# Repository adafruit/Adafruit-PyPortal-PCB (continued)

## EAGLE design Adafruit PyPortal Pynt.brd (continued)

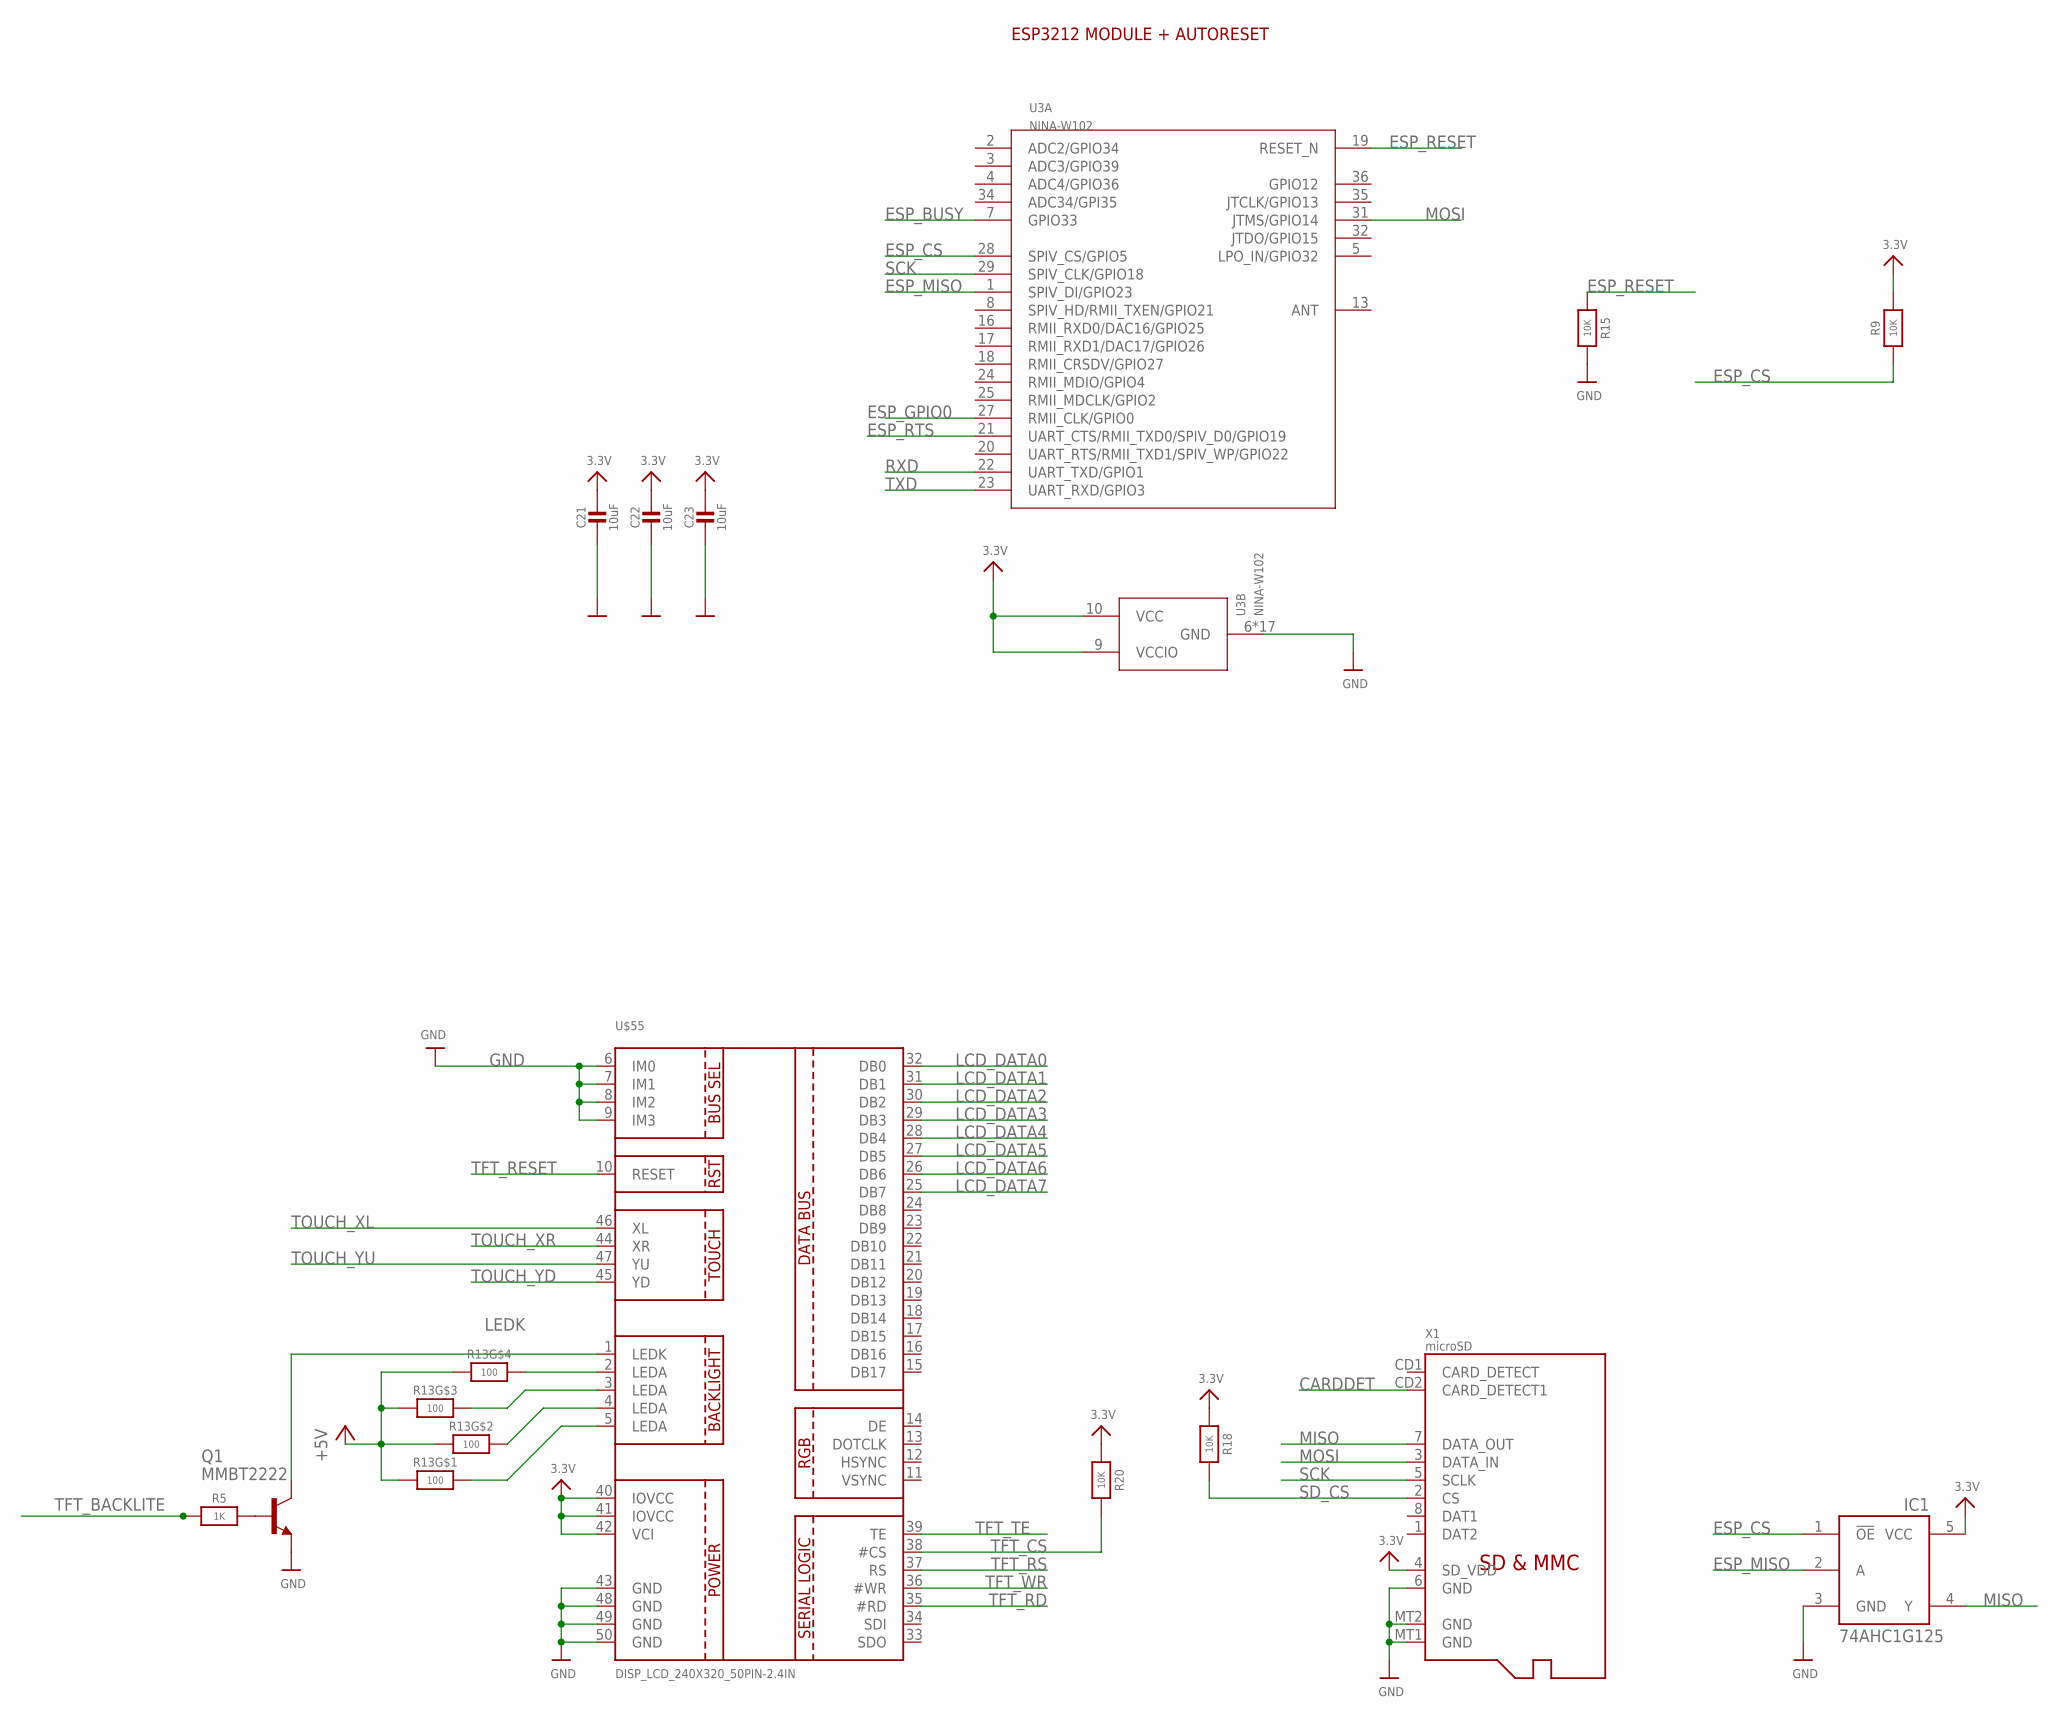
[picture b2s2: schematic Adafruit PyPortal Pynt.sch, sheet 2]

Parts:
C21, C22, C23: 10uF; 0805-NO
IC1: 74AHC1G125; SOT23-5L
Q1: MMBT2222; SOT23-BEC
R5: 1K; 0603-NO
R9, R15, R18, R20: 10K; 0603-NO
R13: 100; RESPACK_4X0603
U3: NINA-W102; ARDUINO-UCS&SOCS_NINA-W1X
U$55: DISP_LCD_240X320_50PIN-2.4IN; TFT_2.4IN_240X320_50PIN
X1: microSD; MICROSD

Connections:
3.3V: C21.1, C22.1, C23.1, IC1.5 (VCC), R9.2, R18.1, R20.1, U3.9 (VCCIO), U3.10 (VCC), U$55.40 (IOVCC), U$55.41 (IOVCC), U$55.42 (VCI), X1.4 (SD_VDD); also elsewhere on the board
+5V: R13.1, R13.2 (1), R13.3 (1), R13.4 (1); also elsewhere on the board
CARDDET: X1.CD2 (CARD_DETECT1); also elsewhere on the board
ESP_BUSY: U3.7 (GPIO33); also elsewhere on the board
ESP_CS: IC1.1 (!OE), R9.1, U3.28 (SPIV_CS/GPIO5); also elsewhere on the board
ESP_GPIO0: U3.27 (RMII_CLK/GPIO0); also elsewhere on the board
ESP_MISO: IC1.2 (A), U3.1 (SPIV_DI/GPIO23)
ESP_RESET: R15.1, U3.19 (RESET_N); also elsewhere on the board
ESP_RTS: U3.21 (UART_CTS/RMII_TXD0/SPIV_D0/GPIO19); also elsewhere on the board
GND: C21.2, C22.2, C23.2, IC1.3 (GND), Q1.E, R15.2, U3.6 (GND), U3.12 (GND), U3.14 (GND), U3.26 (GND), U3.30 (GND), U3.GND@1 (GND), U3.GND@2 (GND), U3.GND@3 (GND), U3.GND@4 (GND), U3.GND@5 (GND), U3.GND@6 (GND), U3.GND@7 (GND), U3.GND@8 (GND), U3.GND@9 (GND), U3.GND@10 (GND), U3.GND@11 (GND), U3.GND@12 (GND), U$55.6 (IM0), U$55.7 (IM1), U$55.8 (IM2), U$55.9 (IM3), U$55.43 (GND), U$55.48 (GND), U$55.49 (GND), U$55.50 (GND), X1.6 (GND), X1.MT1 (GND), X1.MT2 (GND); also elsewhere on the board
LCD_DATA0: U$55.32 (DB0); also elsewhere on the board
LCD_DATA1: U$55.31 (DB1); also elsewhere on the board
LCD_DATA2: U$55.30 (DB2); also elsewhere on the board
LCD_DATA3: U$55.29 (DB3); also elsewhere on the board
LCD_DATA4: U$55.28 (DB4); also elsewhere on the board
LCD_DATA5: U$55.27 (DB5); also elsewhere on the board
LCD_DATA6: U$55.26 (DB6); also elsewhere on the board
LCD_DATA7: U$55.25 (DB7); also elsewhere on the board
LEDK: Q1.C, U$55.1 (LEDK)
MISO: IC1.4 (Y), X1.7 (DATA_OUT); also elsewhere on the board
MOSI: U3.31 (JTMS/GPIO14), X1.3 (DATA_IN); also elsewhere on the board
unnamed: R13.8 (2), U$55.5 (LEDA)
unnamed: R13.5 (2), U$55.2 (LEDA)
unnamed: R13.6 (2), U$55.3 (LEDA)
unnamed: R13.7 (2), U$55.4 (LEDA)
unnamed: Q1.B, R5.2
RXD: U3.22 (UART_TXD/GPIO1); also elsewhere on the board
SCK: U3.29 (SPIV_CLK/GPIO18), X1.5 (SCLK); also elsewhere on the board
SD_CS: R18.2, X1.2 (CS); also elsewhere on the board
TFT_BACKLITE: R5.1; also elsewhere on the board
TFT_CS: R20.2, U$55.38 (#CS); also elsewhere on the board
TFT_RD: U$55.35 (#RD); also elsewhere on the board
TFT_RESET: U$55.10 (RESET); also elsewhere on the board
TFT_RS: U$55.37 (RS); also elsewhere on the board
TFT_TE: U$55.39 (TE); also elsewhere on the board
TFT_WR: U$55.36 (#WR); also elsewhere on the board
TOUCH_XL: U$55.46 (XL); also elsewhere on the board
TOUCH_XR: U$55.44 (XR); also elsewhere on the board
TOUCH_YD: U$55.45 (YD); also elsewhere on the board
TOUCH_YU: U$55.47 (YU); also elsewhere on the board
TXD: U3.23 (UART_RXD/GPIO3); also elsewhere on the board

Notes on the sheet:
ESP3212 MODULE + AUTORESET

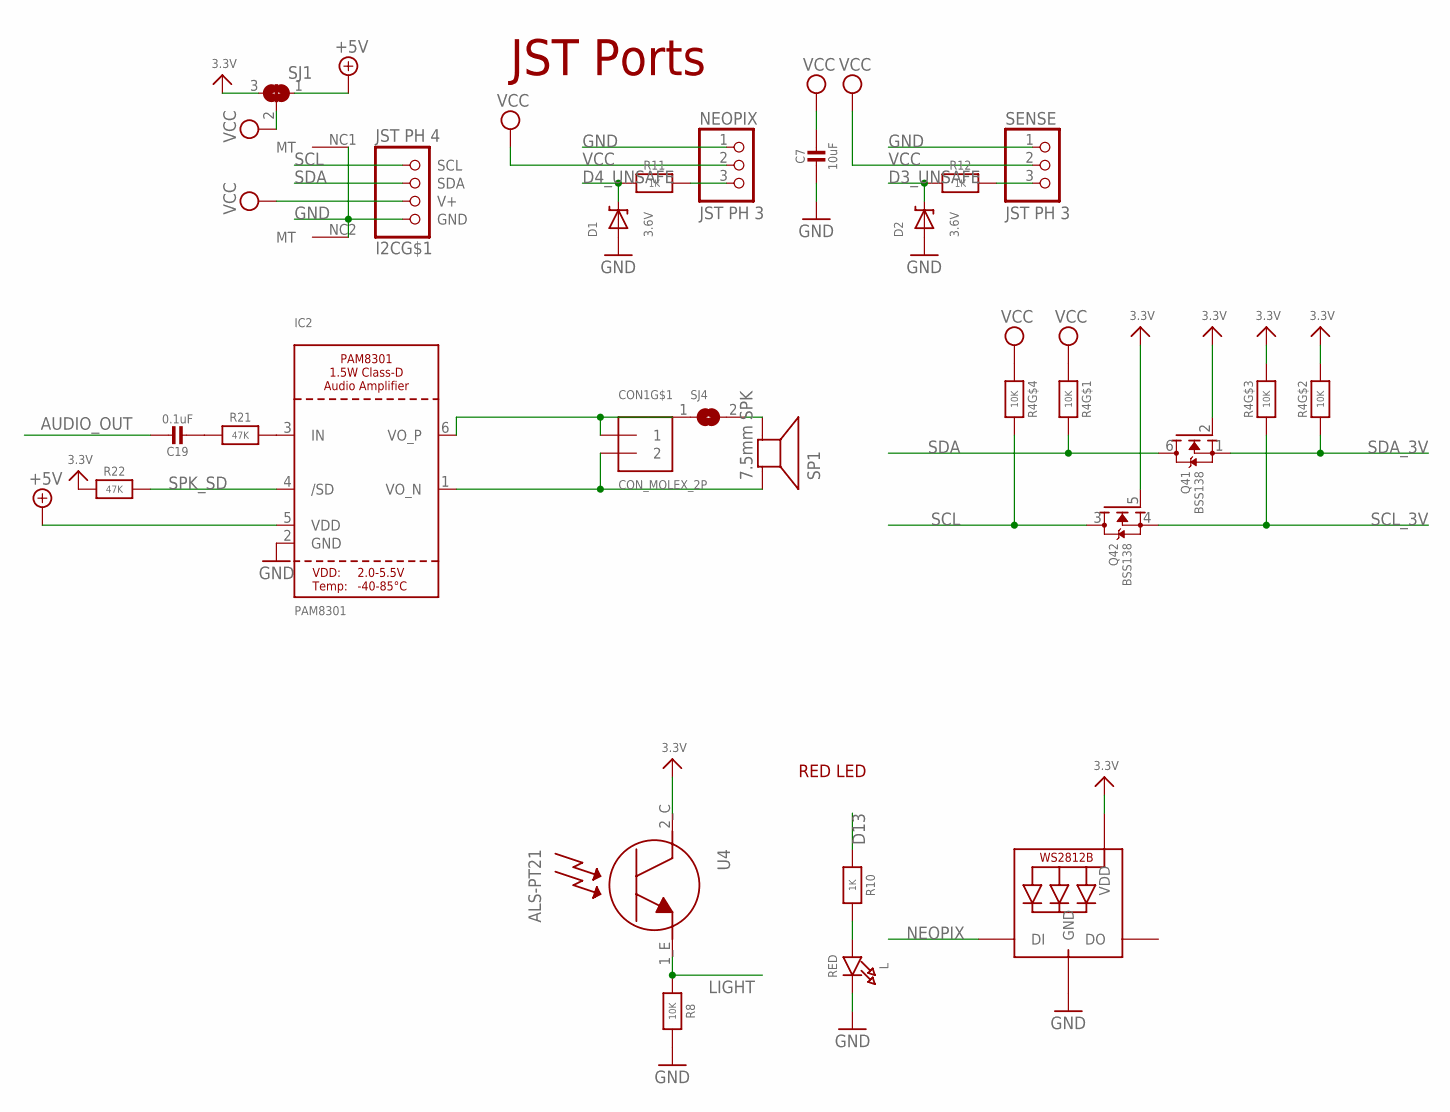
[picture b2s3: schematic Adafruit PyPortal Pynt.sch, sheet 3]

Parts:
C7: 10uF; 0805-NO
C19: 0.1uF; 0603-NO
CON1: CON_MOLEX_2P; 53398-0271
D1, D2: 3.6V; SOD-323
I2C: JST PH 4; JSTPH4
IC2: PAM8301; SOT23-6
L: RED; CHIPLED_0805_NOOUTLINE
LED1: WS2812B3535; LED3535
NEOPIX: JST PH 3; JSTPH3
Q4: BSS138; SOT363
R4: 10K; RESPACK_4X0603
R8: 10K; 0603-NO
R10, R11, R12: 1K; 0603-NO
R21, R22: 47K; 0603-NO
SENSE: JST PH 3; JSTPH3
SJ1: SOLDERJUMPER_2WAY; SOLDERJUMPER_2WAY_OPEN_NOPASTE
SJ4: SOLDERJUMPERCLOSED; SOLDERJUMPER_CLOSEDWIRE
SP1: 7.5mm SPK; BUZZER_SMT_7.5MM
U4: ALS-PT21; ALS-PT26-21C

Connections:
3.3V: LED1.2 (VDD), Q4.2 (G), Q4.5 (G), R4.2 (1), R4.3 (1), R22.1, SJ1.3, U4.2_C (C); also elsewhere on the board
+5V: IC2.5 (VDD), SJ1.1; also elsewhere on the board
AUDIO_OUT: C19.1; also elsewhere on the board
D3: R12.1, SENSE.3
D3_UNSAFE: D2.C, R12.2; also elsewhere on the board
D4: NEOPIX.3, R11.1
D4_UNSAFE: D1.C, R11.2; also elsewhere on the board
D13: R10.1; also elsewhere on the board
GND: C7.2, D1.A, D2.A, I2C.1 (GND), I2C.NC1 (MT), I2C.NC2 (MT), IC2.2 (GND), L.C, LED1.4 (GND), NEOPIX.1, R8.1, SENSE.1; also elsewhere on the board
LIGHT: R8.2, U4.1_E (E); also elsewhere on the board
unnamed: L.A, R10.2
unnamed: C19.2, R21.1
unnamed: IC2.3 (IN), R21.2
unnamed: SJ4.2, SP1.-
NEOPIX: LED1.1 (DI); also elsewhere on the board
SCL: I2C.4 (SCL), Q4.3 (D), R4.5 (2)
SCL_3V: Q4.4 (S), R4.6 (2); also elsewhere on the board
SDA: I2C.3 (SDA), Q4.6 (D), R4.8 (2)
SDA_3V: Q4.1 (S), R4.7 (2); also elsewhere on the board
SPKR+: CON1.2, IC2.1 (VO_N), SP1.+
SPK_SD: IC2.4 (/SD), R22.2; also elsewhere on the board
SPRK-: CON1.1, IC2.6 (VO_P), SJ4.1
VCC: C7.1, I2C.2 (V+), NEOPIX.2, R4.1, R4.4 (1), SENSE.2, SJ1.2

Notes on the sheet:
RED LED
JST Ports

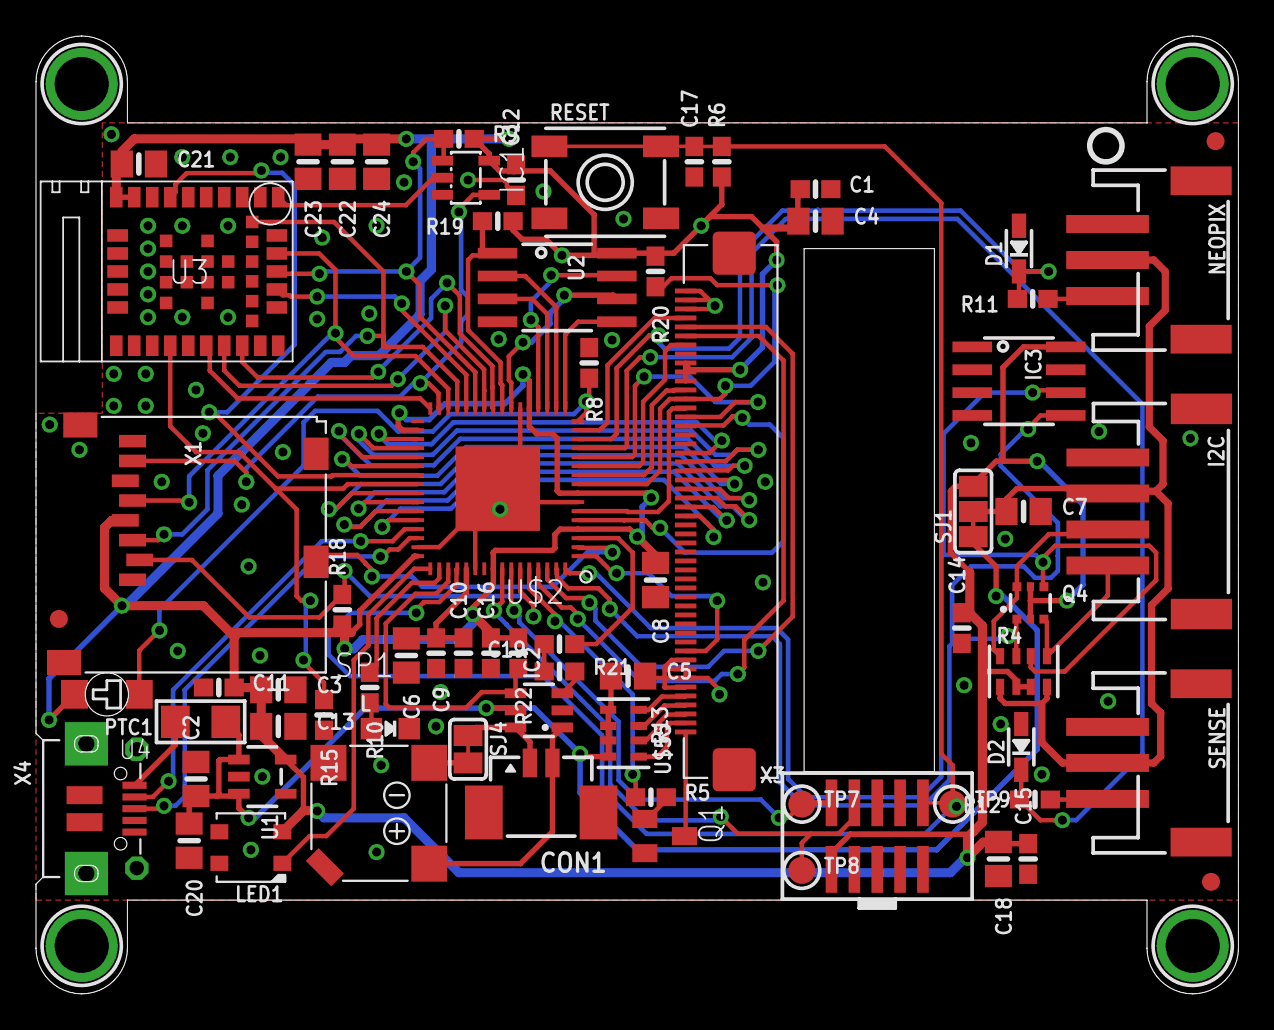
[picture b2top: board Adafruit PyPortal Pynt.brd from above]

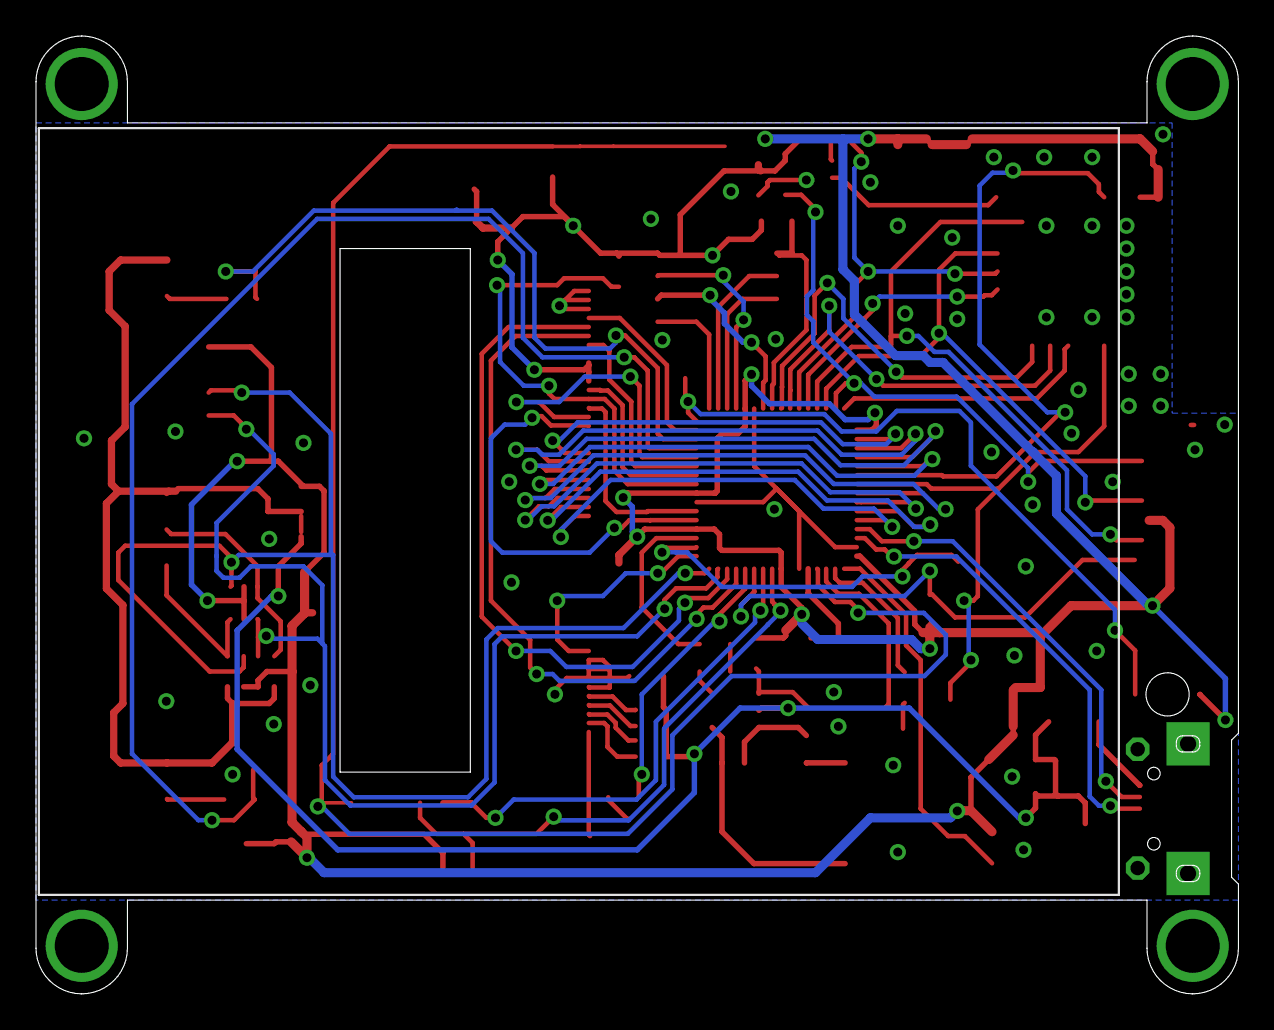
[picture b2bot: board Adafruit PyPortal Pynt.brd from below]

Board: 2 copper layers, 66.8 x 53.2 mm, 79 parts (2 on the bottom side), 74 nets.

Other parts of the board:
U$19: PYPORTALPYNT_TOP
U$54: PYPORTALPYNT_BOT
U$63: PCBFEAT-REV-040

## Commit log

2019-02-26 Add PCB files.
2019-07-17 updated to use cookiecutter for pcb repos
2019-12-19 Adding Pynt PCB
2019-12-19 Adding image asset.
2019-12-20 Adding Titano board files.
2019-12-20 Adding Titano image asset.
2019-12-20 wrong image uploaded.
2019-12-20 Add Titano image asset
2019-12-20 One more time.
2019-12-20 Add Titano image
2022-05-02 Added PyPortal Prettypins
2022-05-11 Added pynt and titano prettypins
